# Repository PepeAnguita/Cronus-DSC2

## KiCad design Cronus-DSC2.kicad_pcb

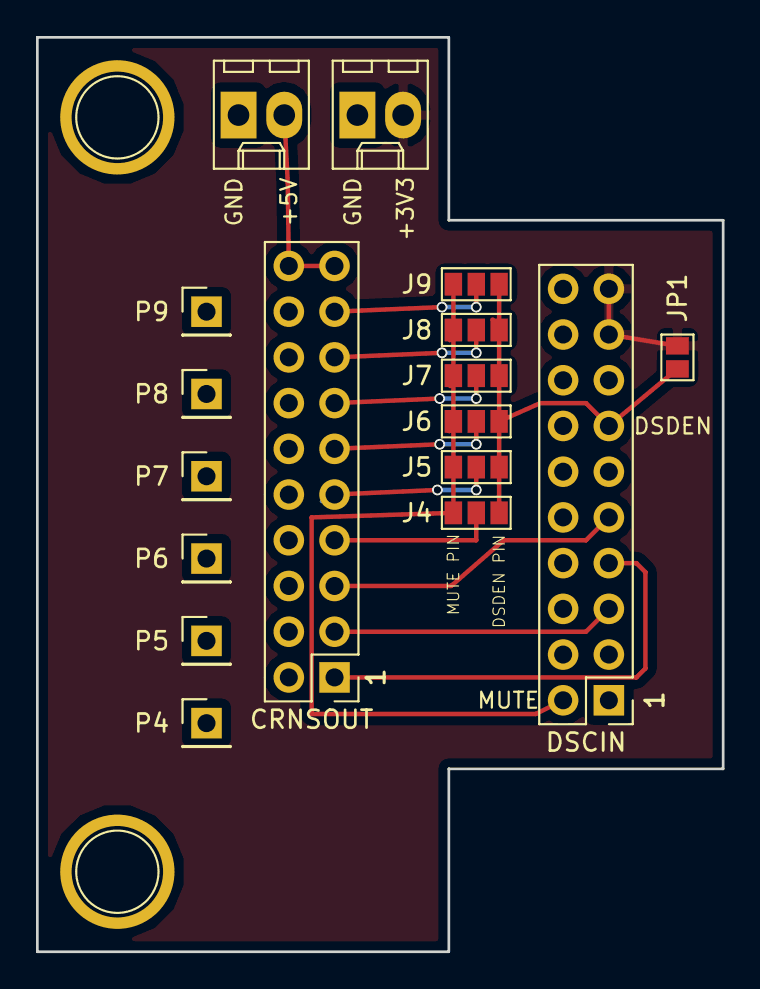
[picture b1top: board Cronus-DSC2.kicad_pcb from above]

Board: 2 copper layers, 38.1 x 50.8 mm, 19 parts (0 on the bottom side), 14 nets.

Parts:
CRNSOUT: CRNSOUT; Pin_Header_Straight_2x10_Top_To_Bottom_Pitch2.54mm
DSCIN: DSC2IN; Pin_Header_Straight_2x10_Top_To_Bottom_Pitch2.54mm
J4: GS4; GS3
J5: GS5; GS3
J6: GS6; GS3
J7: GS7; GS3
J8: GS8; GS3
J9: GS9; GS3
JP1: DSD_EN_3V3; GS2
P4: GND4; Pin_Header_Straight_1x01_Pitch2.54mm
P5: GND5; Pin_Header_Straight_1x01_Pitch2.54mm
P6: GND6; Pin_Header_Straight_1x01_Pitch2.54mm
P7: GND7; Pin_Header_Straight_1x01_Pitch2.54mm
P8: GND8; Pin_Header_Straight_1x01_Pitch2.54mm
P9: GND9; Pin_Header_Straight_1x01_Pitch2.54mm
PWR_3V31: PWR_3V3; Molex_KK-6410-02_02x2.54mm_Straight_Power
PWR_5V1: PWR_5V; Molex_KK-6410-02_02x2.54mm_Straight_Power
REF1, REF2: 1pin

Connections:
GND: CRNSOUT.11, CRNSOUT.12, CRNSOUT.13, CRNSOUT.14, CRNSOUT.15, CRNSOUT.16, CRNSOUT.17, CRNSOUT.18, CRNSOUT.19, DSCIN.8, DSCIN.13, DSCIN.14, DSCIN.15, P4.1, P5.1, P6.1, P7.1, P8.1, P9.1, PWR_3V31.GND, PWR_5V1.GND
unnamed: CRNSOUT.1, DSCIN.4
unnamed: CRNSOUT.2, DSCIN.3
unnamed: CRNSOUT.3, DSCIN.5
unnamed: CRNSOUT.4, J4.2
unnamed: CRNSOUT.5, J5.2
unnamed: CRNSOUT.6, J6.2
unnamed: CRNSOUT.7, J7.2
unnamed: CRNSOUT.8, J8.2
unnamed: CRNSOUT.9, J9.2
unnamed: DSCIN.7, J4.3, J5.3, J6.3, J7.3, J8.3, J9.3, JP1.1
unnamed: DSCIN.11, J4.1, J5.1, J6.1, J7.1, J8.1, J9.1
VCC: CRNSOUT.10, CRNSOUT.20, PWR_5V1.VCC
VDD: DSCIN.9, DSCIN.10, JP1.2, PWR_3V31.VCC

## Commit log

2018-04-22 Complete PCB as it was submitted to OSHPark
2018-04-22 Temporary solution until I learn KiCad properly
2018-04-22 Renamed the project files. Pruned some files.
2018-04-22 Kicad 5.0
